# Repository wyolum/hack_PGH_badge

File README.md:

# hack_PGH_badge
* Badge PCB kit for hackPGH, for "learn to solder" and "learn to lasercut" classes
* Can be used for basic soldering (through hole parts) or advanced soldering (surface mount parts)

***FEATURES***
1. Four LED's with series current limit resistors
2. Two CR2032 Coin Batteries
3. Use slow fade multi-color LEDs, or all White LEDs or whatever you choose
5. The simple version is just battery, resistors and LEDs.
6. The fancy version is with two US1881 magnetic hall latch sensors - see notes in the schematic (PDF)

***RENDERS***
rev1 renders

License
-------
[CERN Open Hardware Licence v1.2 ]

[CERN Open Hardware Licence v1.2 ]:http://www.ohwr.org/attachments/2388/cern_ohl_v_1_2.txt

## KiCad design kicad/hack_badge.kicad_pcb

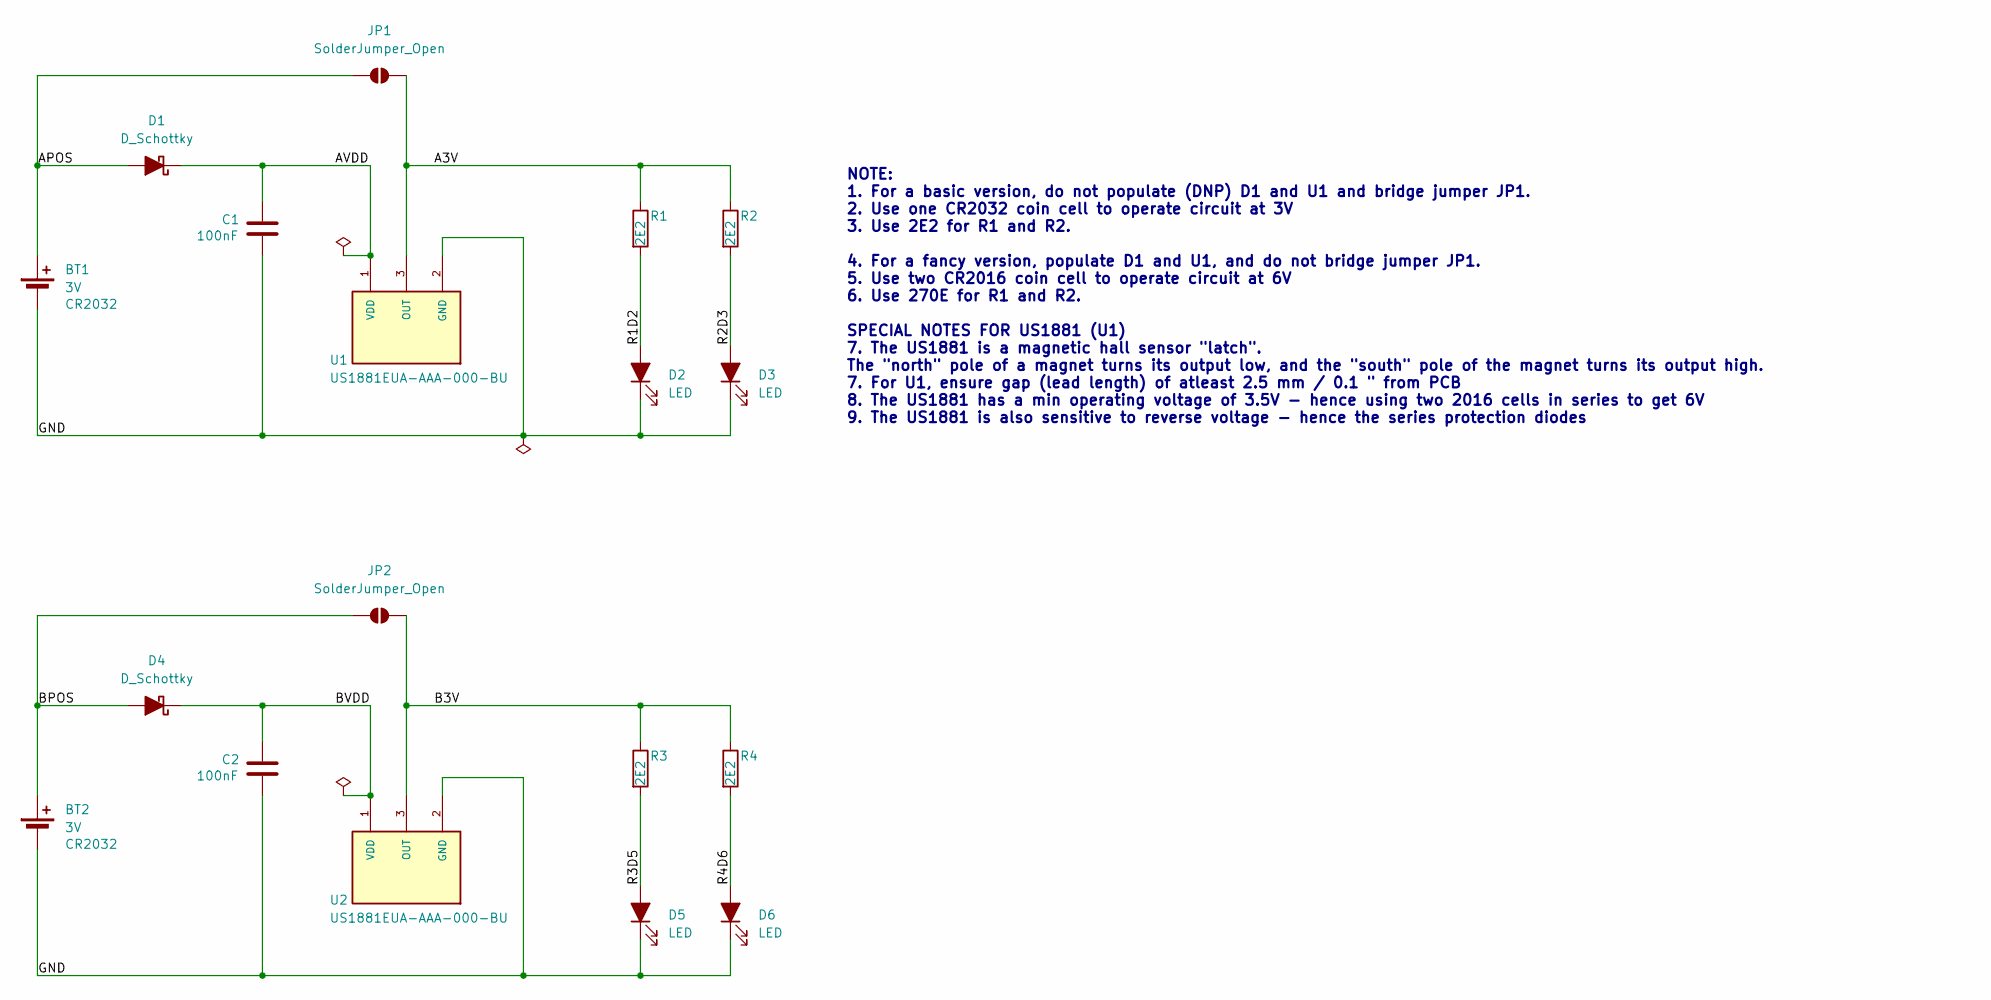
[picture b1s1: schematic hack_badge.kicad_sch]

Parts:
BT1, BT2: 3V; BatteryHolder_Keystone_3002_1x2032
C1, C2: 100nF; C_Disc_D3.0mm_W1.6mm_P2.50mm
D1, D4: D_Schottky; D_SOD-123_DO-34_SOD68_P7.62mm_Horizontal
D2, D3, D5, D6: LED; LED_D3.0mm_Dialight_598
JP1, JP2: SolderJumper_Open; SolderJumper-2_P1.3mm_Open_RoundedPad1.0x1.5mm
R1, R2, R3, R4: 2E2; R_1206_Axial_DIN0204_L3.6mm_D1.6mm_P7.62mm_Horizontal
U1, U2: US1881EUA-AAA-000-BU; TO92127P410H430-3_TSOT-23; PARTREV 010

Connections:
/A3V: JP1.2 (B), R1.1, R2.1, U1.3 (OUT)
/APOS: BT1.1 (+), D1.2 (A), JP1.1 (A)
/AVDD: C1.1, D1.1 (K), U1.1 (VDD)
/B3V: JP2.2 (B), R3.1, R4.1, U2.3 (OUT)
/BPOS: BT2.1 (+), D4.2 (A), JP2.1 (A)
/BVDD: C2.1, D4.1 (K), U2.1 (VDD)
/GND: BT1.2 (-), BT2.2 (-), C1.2, C2.2, D2.1 (K), D3.1 (K), D5.1 (K), D6.1 (K), U1.2 (GND), U2.2 (GND)
/R1D2: D2.2 (A), R1.2
/R2D3: D3.2 (A), R2.2
/R3D5: D5.2 (A), R3.2
/R4D6: D6.2 (A), R4.2

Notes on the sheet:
NOTE: 1. For a basic version, do not populate (DNP) D1 and U1 and bridge jumper JP1. 2. Use one CR2032 coin cell to operate circuit at 3V 3. Use 2E2 for R1 and R2. 4. For a fancy version, populate D1 and U1, and do not bridge jumper JP1. 5. Use two CR2016 coin cell to operate circuit at 6V 6. Use 2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

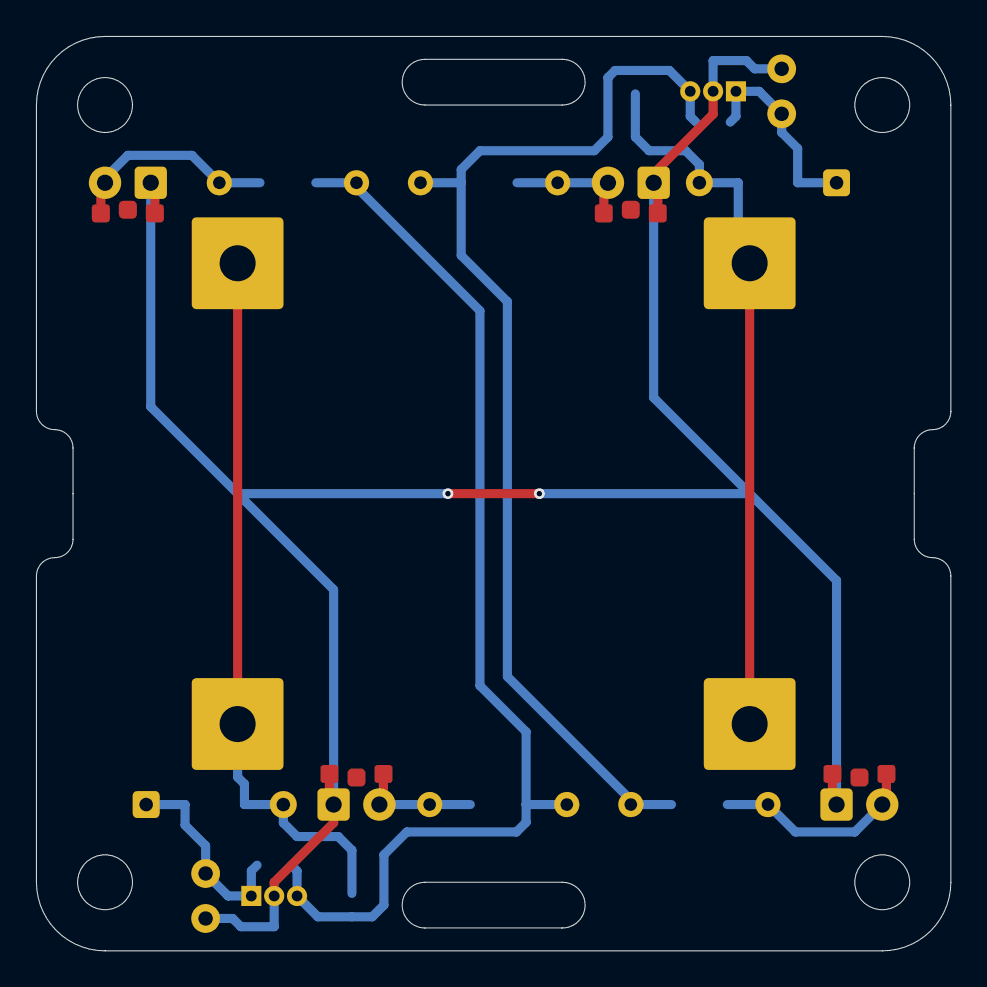
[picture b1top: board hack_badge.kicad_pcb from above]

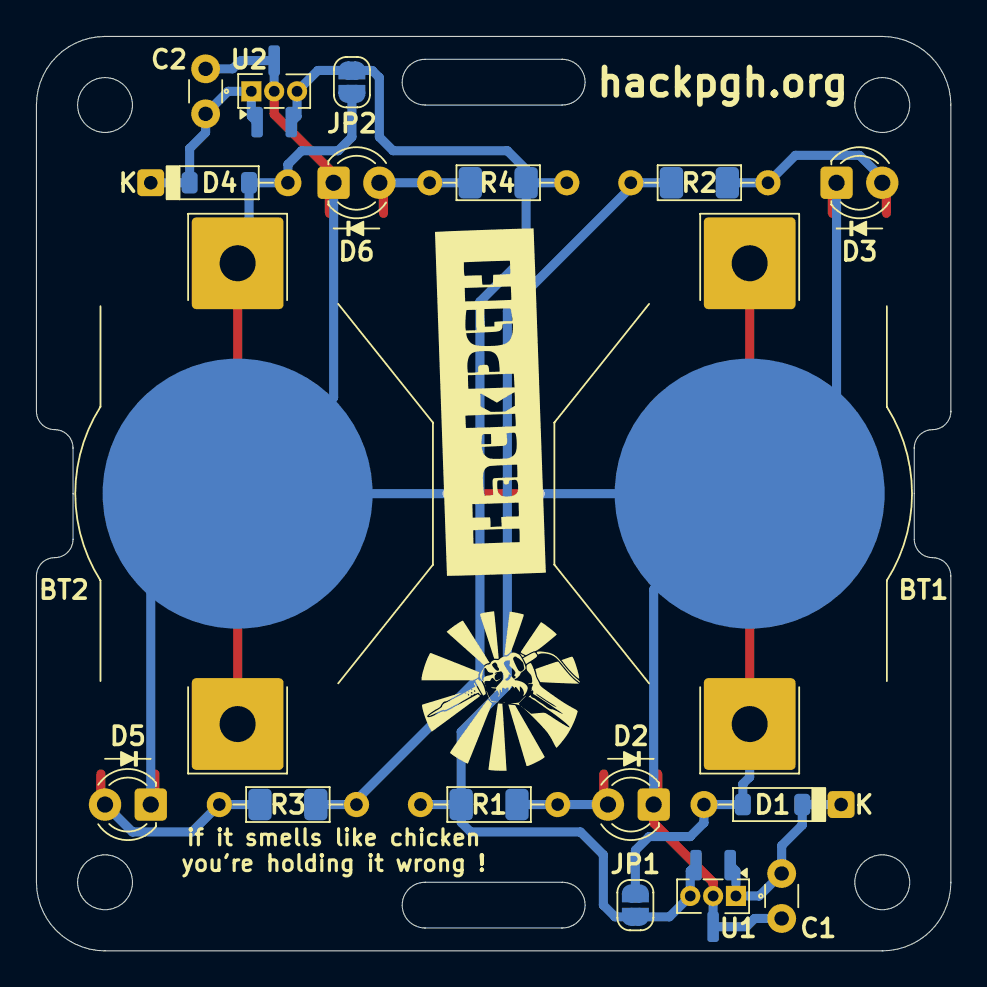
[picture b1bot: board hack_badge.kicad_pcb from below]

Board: 2 copper layers, 50.8 x 50.8 mm, 18 parts (14 on the bottom side), 11 nets.

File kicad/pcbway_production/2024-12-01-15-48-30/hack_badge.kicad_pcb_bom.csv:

Designator,Quantity,Value,Footprint,Package,MPN,DNP,Mount_Type,Description,MF,MAXIMUM_PACKAGE_HEIGHT,Check_prices,STANDARD,PARTREV,SnapEDA_Link,MP,Description_1
"BT1, BT2",2,3V,BatteryHolder_Keystone_3002_1x2032,,,,smt,CR2032,,,,,,,,
"C1, C2",2,100nF,C_Disc_D3.0mm_W1.6mm_P2.50mm,,,,tht,Unpolarized capacitor,,,,,,,,
"D1, D4",2,D_Schottky,D_SOD-123_DO-34_SOD68_P7.62mm_Horizontal,,,,tht,"Schottky diode, filled shape",,,,,,,,
"D2, D3, D5, D6",4,LED,LED_D3.0mm_Dialight_598,,,,tht,"Light emitting diode, filled shape",,,,,,,,
"R1, R2, R3, R4",4,2E2,R_1206_Axial_DIN0204_L3.6mm_D1.6mm_P7.62mm_Horizontal,,,,tht,Resistor,,,,,,,,
"U1, U2",2,US1881EUA-AAA-000-BU,TO92127P410H430-3_TSOT-23,TO-92-3L-3 Melexis,,,tht,,Melexis Technologies,4.3mm,https://www.snapeda.com/parts/US1881EUA-AAA-000-BU/Melexis+T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,IPC-2221/IPC-2222,010,https://www.snapeda.com/parts/US1881EUA-AAA-000-BU/Melexis+T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,US1881EUA-AAA-000-BU,Digital Switch Latch Open Drain Hall Effect TO-92-3

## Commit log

2024-12-01 Update README.md
    added renders
2024-12-03 complete
2024-12-13 added improved logo
